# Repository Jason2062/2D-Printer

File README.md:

# 2D-Printer
This project is a realtime writing machine, which enable user to write information remotely. This design controls the movement of the pen on the x and y axes through two stepping motors and the up and down movement of the pen through a servo motor. The [Wiki page](https://github.com/Jason2062/2D-Printer/wiki) details how to recreate the machine.<br>

 # Software Design
 
# Flow Chart

The program is triggered by mouse clicks and movements. When the user moving the mouse, according to the comparison results of the x and y axis coordinates with their previous values, different threads are triggered to control the stepper motor rotating clockwise or anticlockwise and realize the x and y axis movement control of the pen. When the mouse is clicked, the Raspberry Pi switch the servo motor state to realize the pen point moving up and down. Besides, the GUI porvides the path record to facilitate the user to see the pattern printed by the 2D printer. 

# Required Package
## How to install QT5 and QT Creator
```
sudo apt-get update
sudo apt-get upgrade 

//Install QT5 

sudo apt-get install qt5-default

//Install QT creator

sudo apt-get install qtcreator
```
## How to install wiringPi

```
git clone git://git.drogon.net/wiringPi

cd wiringPi
./build

Type "gpio -v" to test

Type "gpio readall" to check pin information
```

# Documentation

[Doxygen documentation](http://htmlpreview.github.io/?https://github.com/Jason2062/2D-Printer/blob/master/Doxygen/html/annotated.html)

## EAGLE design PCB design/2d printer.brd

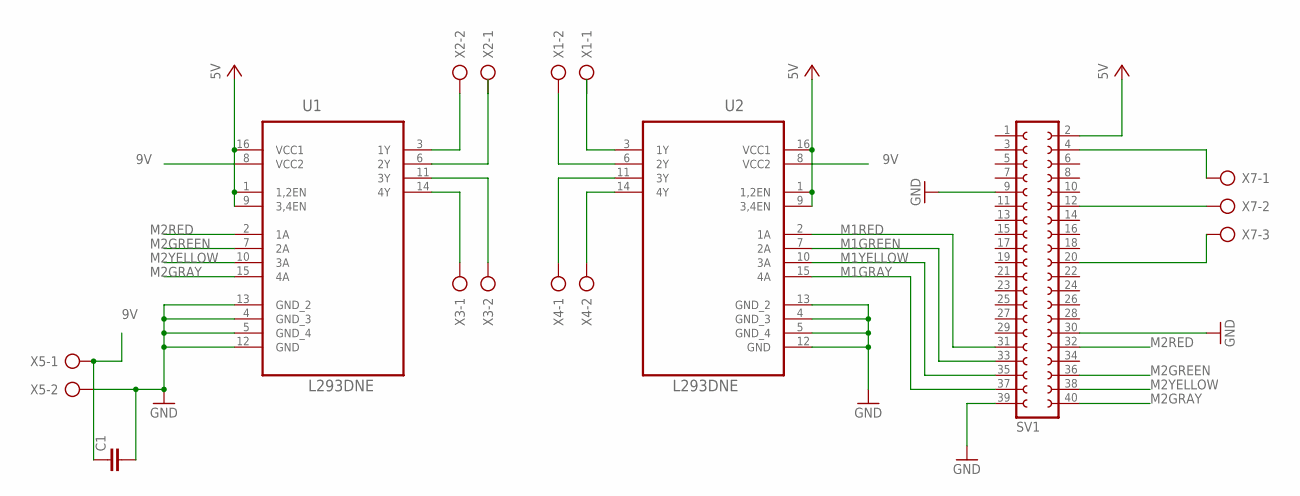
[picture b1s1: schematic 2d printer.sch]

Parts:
C1: C2.5/2; C2.5-2
SV1: FE20-2
U1, U2: L293DNE; DIP254P762X508-16
X1, X2, X3, X4, X5: AK300/2
X7: AK300/3

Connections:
9V: C1.1, U1.8 (VCC2), U2.8 (VCC2), X5.1
GND: C1.2, SV1.9, SV1.30, SV1.39, U1.4 (GND_3), U1.5 (GND_4), U1.12 (GND), U1.13 (GND_2), U2.4 (GND_3), U2.5 (GND_4), U2.12 (GND), U2.13 (GND_2), X5.2
M1GRAY: SV1.37, U2.15 (4A)
M1GREEN: SV1.33, U2.7 (2A)
M1RED: SV1.31, U2.2 (1A)
M1YELLOW: SV1.35, U2.10 (3A)
M2GRAY: SV1.40, U1.15 (4A)
M2GREEN: SV1.36, U1.7 (2A)
M2RED: SV1.32, U1.2 (1A)
M2YELLOW: SV1.38, U1.10 (3A)
unnamed: U2.3 (1Y), X1.1
unnamed: U1.3 (1Y), X2.2
unnamed: U1.6 (2Y), X2.1
unnamed: U1.14 (4Y), X3.1
unnamed: U1.11 (3Y), X3.2
unnamed: U2.14 (4Y), X4.2
unnamed: U2.6 (2Y), X1.2
unnamed: U2.11 (3Y), X4.1
unnamed: SV1.4, X7.1
unnamed: SV1.20, X7.3
unnamed: SV1.12, X7.2
VCC: SV1.2, U1.1 (1,2EN), U1.9 (3,4EN), U1.16 (VCC1), U2.1 (1,2EN), U2.9 (3,4EN), U2.16 (VCC1)

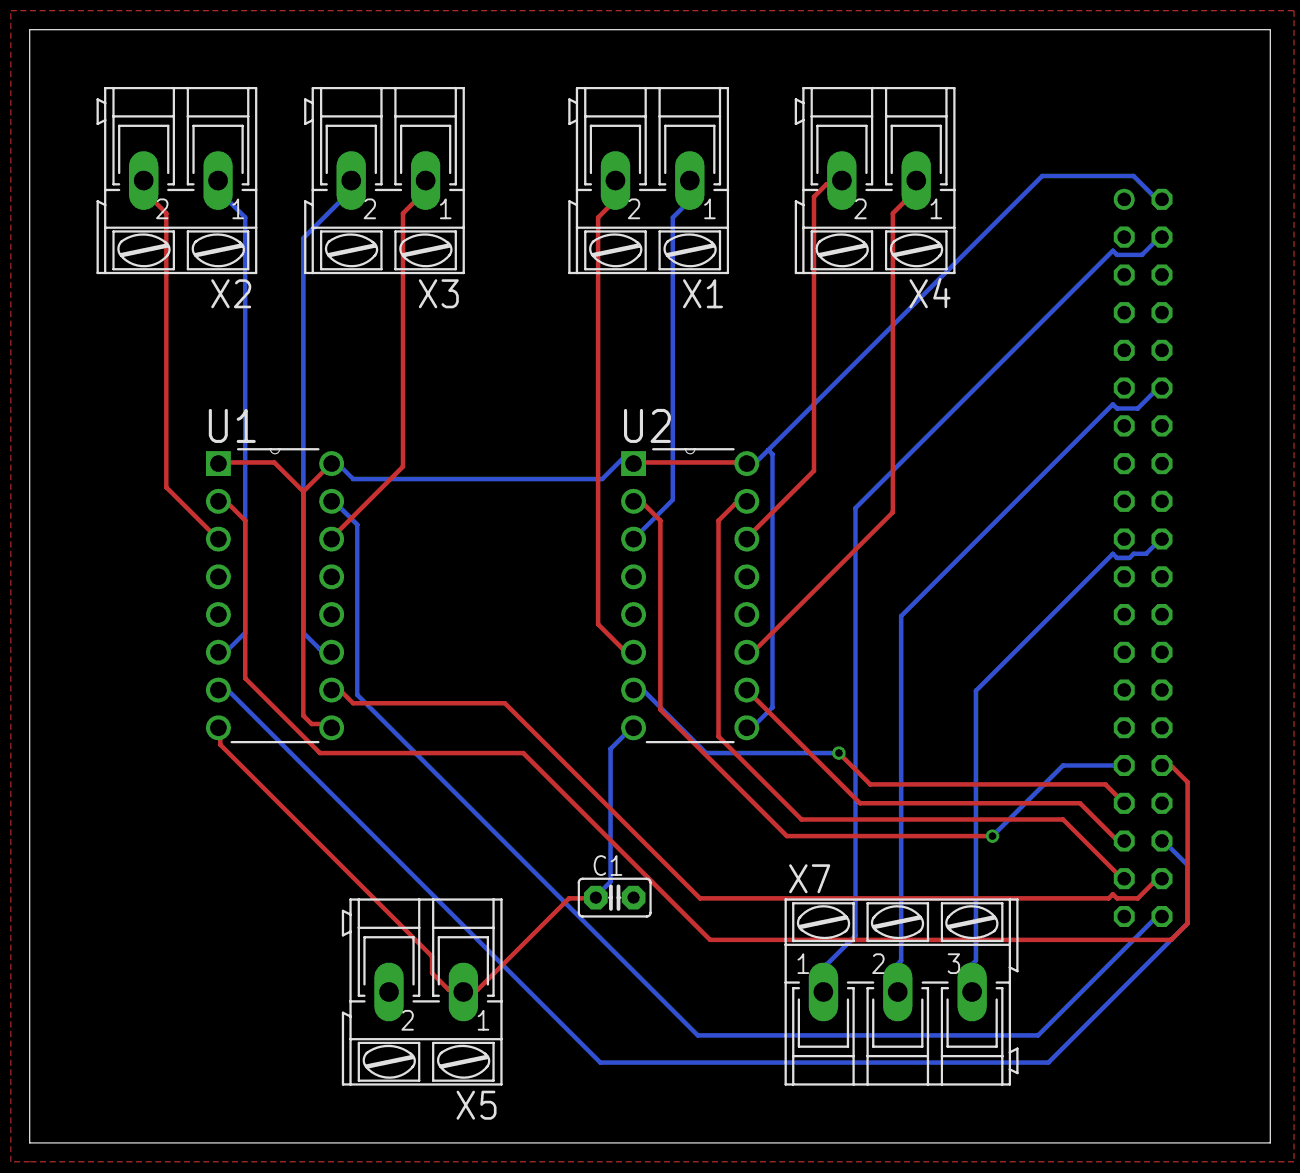
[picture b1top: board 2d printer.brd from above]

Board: 2 copper layers, 83.5 x 74.9 mm, 10 parts (1 on the bottom side), 22 nets.

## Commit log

2019-02-19 Create QMouseEvent
2019-02-19 Update and rename readme to ReadMe
2019-04-13 Create PrinterGUI
2019-04-14 Add files via upload
    uml
2019-04-14 Add files via upload
    Doxygen
2019-04-14 Add files via upload
    oxygen
2019-04-14 Add files via upload
    doxyfile
2019-04-14 Add files via upload
    PCB
